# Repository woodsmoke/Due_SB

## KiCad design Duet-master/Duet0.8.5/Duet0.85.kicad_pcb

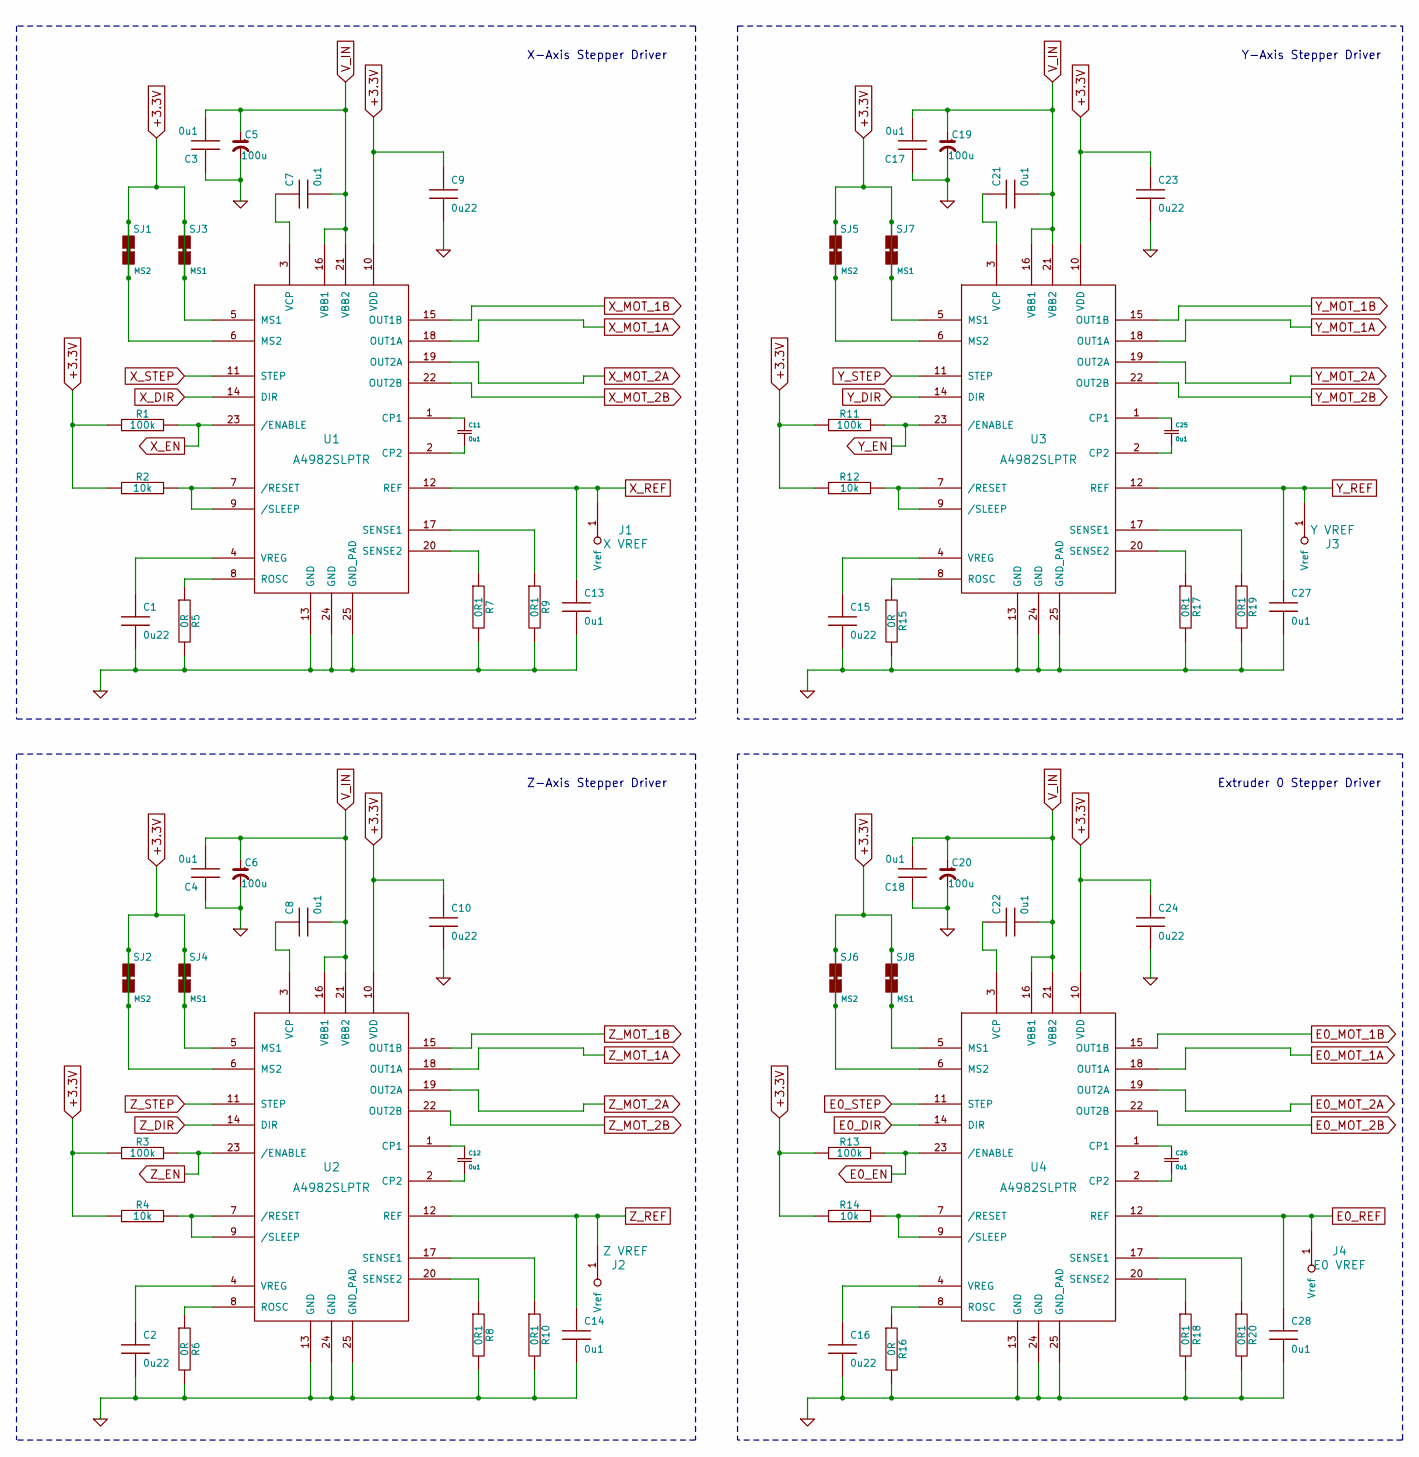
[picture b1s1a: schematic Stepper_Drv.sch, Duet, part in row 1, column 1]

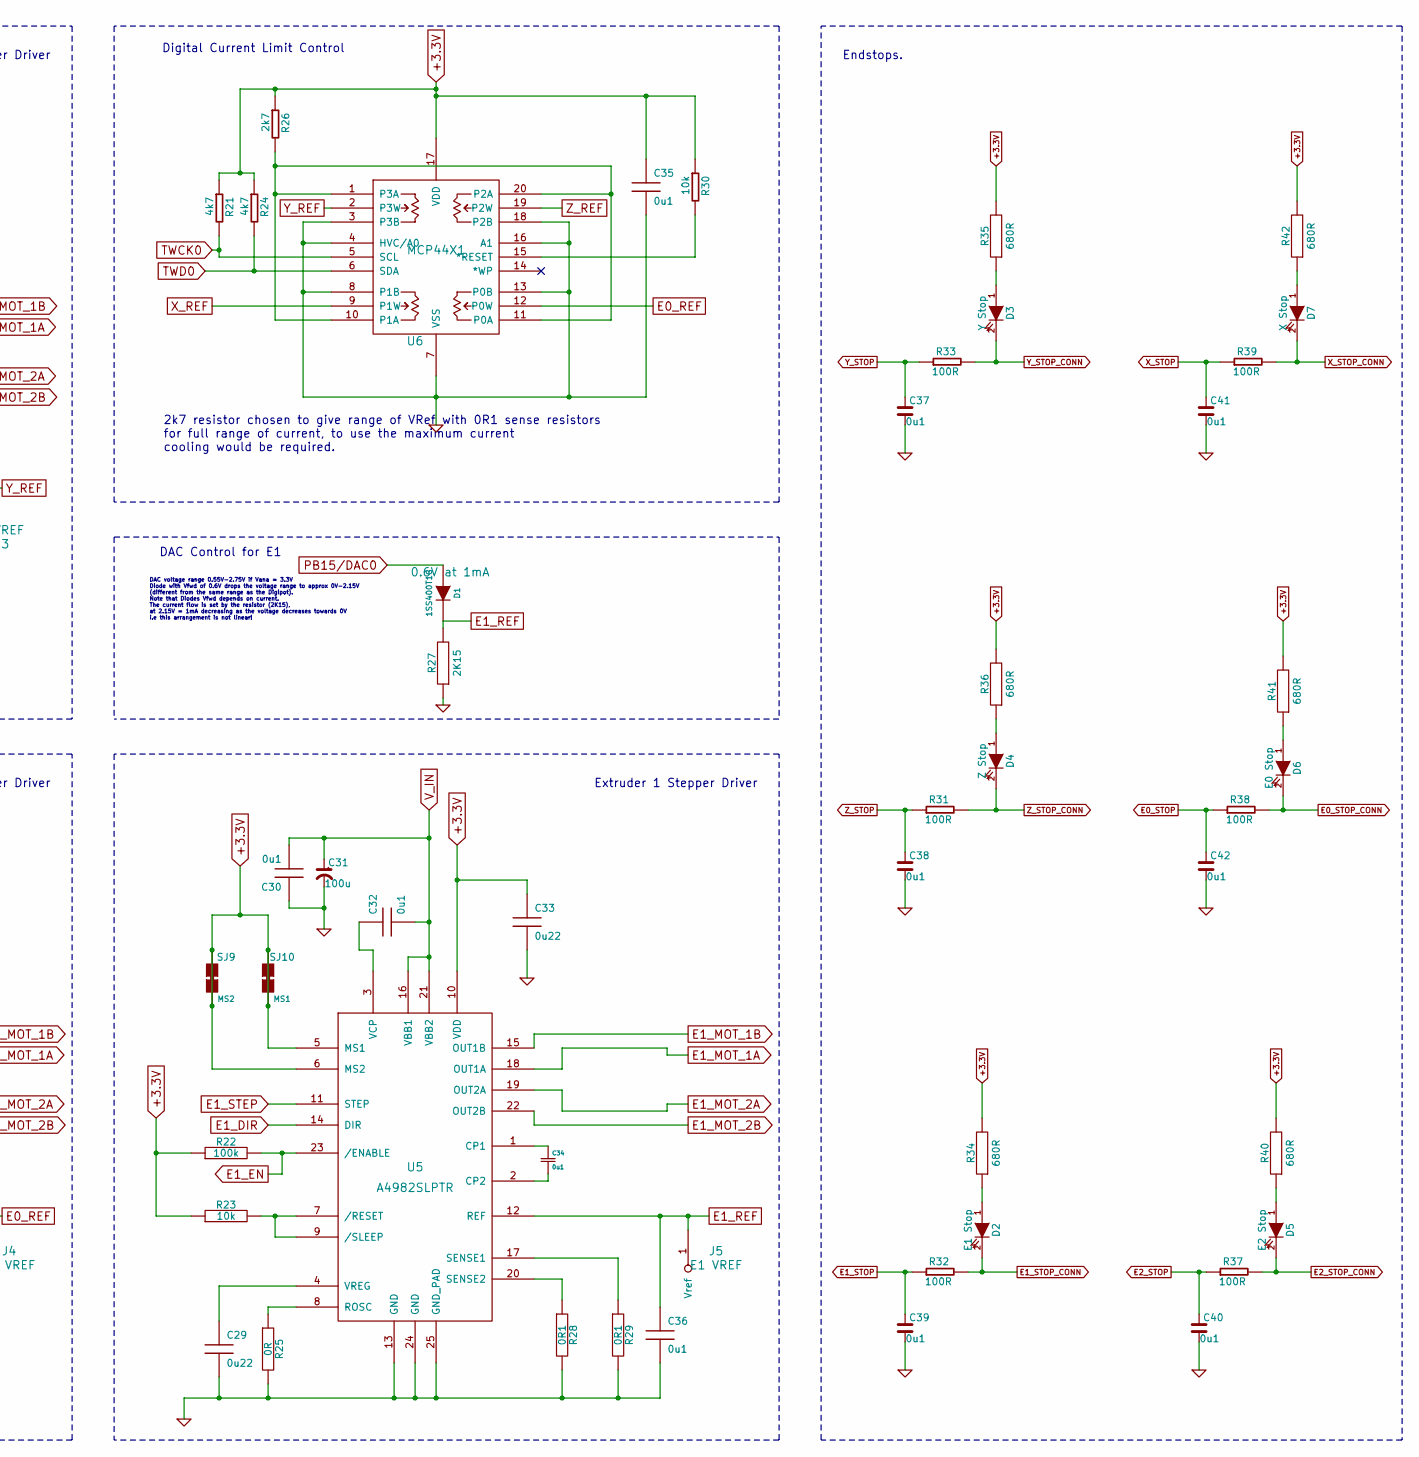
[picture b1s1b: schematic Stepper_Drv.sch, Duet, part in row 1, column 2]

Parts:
C1, C2, C9, C10, C15, C16, C23, C24, C29, C33: 0u22; 0mf22_capacitor
C3, C4, C7, C8, C11, C12, C13, C14, C17, C18, C21, C22, C25, C26, C27, C28, C30, C32, C34, C35, C36, C37, C38, C39, C40, C41, C42: 0u1; 0mf1_capacitor
C5, C6, C19, C20, C31: 100u; 100mf_capacitor
D1: 1SS400T1G; Fwd Voltage Drop (1mA) 0.6V at 1mA
D2: E1 Stop; E1STOP_diode
D3: Y Stop; YSTOP_diode
D4: Z Stop; ZSTOP_diode
D5: E2 Stop; E2STOP_diode
D6: E0 Stop; E0STOP_diode
D7: X Stop; XSTOP_diode
J1: X VREF; Vref
J2: Z VREF; Vref
J3: Y VREF; Vref
J4: E0 VREF; Vref
J5: E1 VREF; Vref
R1, R3, R11, R13, R22: 100k; 100k_R_0603
R2, R4, R12, R14, R23, R30: 10k; 10k_R_0603
R5, R6, R15, R16, R25: 0R; 0R_R_0603
R7, R8, R9, R10, R17, R18, R19, R20, R28, R29: 0R1; 0R1_R_1206
R21, R24: 4k7; 4k7_R_0603
R26: 2k7; 2k7_R_0603
R27: 2K15; 2k15_R_0603
R31: 100R; 100k_R_0603
R32, R33, R37, R38, R39: 100R; 100R_R_0603
R34, R35, R36, R40, R41, R42: 680R; 680R_R_0603
SJ1, SJ2, SJ5, SJ6, SJ9: MS2; SJump
SJ3, SJ4, SJ7, SJ8, SJ10: MS1; SJump
U1, U2, U3, U4, U5: A4982SLPTR; A4982SPLTR_TSSOP-24-thin_pads
U6: MCP44X1; MCP44X1_TSSOP-20

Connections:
+3.3V: C9.1, C10.1, C23.1, C24.1, C33.1, C35.1, R1.1, R2.1, R3.1, R4.1, R11.1, R12.1, R13.1, R14.1, R21.1, R22.1, R23.1, R24.1, R26.1, R30.1, R34.2, R35.2, R36.2, R40.2, R41.2, R42.2, SJ1.1 (SJ_P1), SJ1.2 (SJ_P2), SJ2.1 (SJ_P1), SJ2.2 (SJ_P2), SJ3.1 (SJ_P1), SJ3.2 (SJ_P2), SJ4.1 (SJ_P1), SJ4.2 (SJ_P2), SJ5.1 (SJ_P1), SJ5.2 (SJ_P2), SJ6.1 (SJ_P1), SJ6.2 (SJ_P2), SJ7.1 (SJ_P1), SJ7.2 (SJ_P2), SJ8.1 (SJ_P1), SJ8.2 (SJ_P2), SJ9.1 (SJ_P1), SJ9.2 (SJ_P2), SJ10.1 (SJ_P1), SJ10.2 (SJ_P2), U1.5 (MS1), U1.6 (MS2), U1.10 (VDD), U2.5 (MS1), U2.6 (MS2), U2.10 (VDD), U3.5 (MS1), U3.6 (MS2), U3.10 (VDD), U4.5 (MS1), U4.6 (MS2), U4.10 (VDD), U5.5 (MS1), U5.6 (MS2), U5.10 (VDD), U6.17 (VDD); also elsewhere on the board
E0_DIR: U4.14 (DIR); also elsewhere on the board
E0_EN: R13.2, U4.23 (/ENABLE); also elsewhere on the board
E0_MOT_1A: U4.18 (OUT1A); also elsewhere on the board
E0_MOT_1B: U4.15 (OUT1B); also elsewhere on the board
E0_MOT_2A: U4.19 (OUT2A); also elsewhere on the board
E0_MOT_2B: U4.22 (OUT2B); also elsewhere on the board
E0_REF: C28.1, J4.1, U4.12 (REF), U6.12 (P0W)
E0_STEP: U4.11 (STEP); also elsewhere on the board
E0_STOP: C42.1, R38.1; also elsewhere on the board
E0_STOP_CONN: D6.2 (K), R38.2; also elsewhere on the board
E1_DIR: U5.14 (DIR); also elsewhere on the board
E1_EN: R22.2, U5.23 (/ENABLE); also elsewhere on the board
E1_MOT_1A: U5.18 (OUT1A); also elsewhere on the board
E1_MOT_1B: U5.15 (OUT1B); also elsewhere on the board
E1_MOT_2A: U5.19 (OUT2A); also elsewhere on the board
E1_MOT_2B: U5.22 (OUT2B); also elsewhere on the board
E1_REF: C36.1, D1.1 (K), J5.1, R27.2, U5.12 (REF)
E1_STEP: U5.11 (STEP); also elsewhere on the board
E1_STOP: C39.1, R32.1; also elsewhere on the board
E1_STOP_CONN: D2.2 (K), R32.2; also elsewhere on the board
E2_STOP: C40.1, R37.1; also elsewhere on the board
E2_STOP_CONN: D5.2 (K), R37.2; also elsewhere on the board
GND: C1.2, C2.2, C3.1, C4.1, C5.2, C6.2, C9.2, C10.2, C13.2, C14.2, C15.2, C16.2, C17.1, C18.1, C19.2, C20.2, C23.2, C24.2, C27.2, C28.2, C29.2, C30.1, C31.2, C33.2, C35.2, C36.2, C37.2, C38.2, C39.2, C40.2, C41.2, C42.2, R5.2, R6.2, R7.2, R8.2, R9.2, R10.2, R15.2, R16.2, R17.2, R18.2, R19.2, R20.2, R25.2, R27.1, R28.2, R29.2, U1.13 (GND), U1.24 (GND), U1.25 (GND_PAD), U2.13 (GND), U2.24 (GND), U2.25 (GND_PAD), U3.13 (GND), U3.24 (GND), U3.25 (GND_PAD), U4.13 (GND), U4.24 (GND), U4.25 (GND_PAD), U5.13 (GND), U5.24 (GND), U5.25 (GND_PAD), U6.3 (P3B), U6.4 (HVC/A0), U6.7 (VSS), U6.8 (P1B), U6.13 (P0B), U6.16 (A1), U6.18 (P2B); also elsewhere on the board
unnamed: C1.1, U1.4 (VREG)
unnamed: C2.1, U2.4 (VREG)
unnamed: C7.1, U1.3 (VCP)
unnamed: C8.1, U2.3 (VCP)
unnamed: C11.1, U1.1 (CP1)
unnamed: C11.2, U1.2 (CP2)
unnamed: C12.1, U2.1 (CP1)
unnamed: C12.2, U2.2 (CP2)
unnamed: C15.1, U3.4 (VREG)
unnamed: C16.1, U4.4 (VREG)
unnamed: C21.1, U3.3 (VCP)
unnamed: C22.1, U4.3 (VCP)
unnamed: C25.1, U3.1 (CP1)
unnamed: C25.2, U3.2 (CP2)
unnamed: C26.1, U4.1 (CP1)
unnamed: C26.2, U4.2 (CP2)
unnamed: C29.1, U5.4 (VREG)
unnamed: C32.1, U5.3 (VCP)
unnamed: C34.1, U5.1 (CP1)
unnamed: C34.2, U5.2 (CP2)
unnamed: D2.1 (A), R34.1
unnamed: D3.1 (A), R35.1
unnamed: D4.1 (A), R36.1
unnamed: D5.1 (A), R40.1
unnamed: D6.1 (A), R41.1
unnamed: D7.1 (A), R42.1
unnamed: R2.2, U1.7 (/RESET), U1.9 (/SLEEP)
unnamed: R4.2, U2.7 (/RESET), U2.9 (/SLEEP)
unnamed: R5.1, U1.8 (ROSC)
unnamed: R6.1, U2.8 (ROSC)
unnamed: R7.1, U1.20 (SENSE2)
unnamed: R8.1, U2.20 (SENSE2)
unnamed: R9.1, U1.17 (SENSE1)
unnamed: R10.1, U2.17 (SENSE1)
unnamed: R12.2, U3.7 (/RESET), U3.9 (/SLEEP)
unnamed: R14.2, U4.7 (/RESET), U4.9 (/SLEEP)
unnamed: R15.1, U3.8 (ROSC)
unnamed: R16.1, U4.8 (ROSC)
unnamed: R17.1, U3.20 (SENSE2)
unnamed: R18.1, U4.20 (SENSE2)
unnamed: R19.1, U3.17 (SENSE1)
unnamed: R20.1, U4.17 (SENSE1)
unnamed: R23.2, U5.7 (/RESET), U5.9 (/SLEEP)
unnamed: R25.1, U5.8 (ROSC)
unnamed: R26.2, U6.1 (P3A), U6.10 (P1A), U6.11 (P0A), U6.20 (P2A)
unnamed: R28.1, U5.20 (SENSE2)
unnamed: R29.1, U5.17 (SENSE1)
unnamed: R30.2, U6.15 (*RESET)
PB15/DAC0: D1.2 (A); also elsewhere on the board
TWCK0: R21.2, U6.5 (SCL); also elsewhere on the board
TWD0: R24.2, U6.6 (SDA); also elsewhere on the board
V_IN: C3.2, C4.2, C5.1, C6.1, C7.2, C8.2, C17.2, C18.2, C19.1, C20.1, C21.2, C22.2, C30.2, C31.1, C32.2, U1.16 (VBB1), U1.21 (VBB2), U2.16 (VBB1), U2.21 (VBB2), U3.16 (VBB1), U3.21 (VBB2), U4.16 (VBB1), U4.21 (VBB2), U5.16 (VBB1), U5.21 (VBB2); also elsewhere on the board
X_DIR: U1.14 (DIR); also elsewhere on the board
X_EN: R1.2, U1.23 (/ENABLE); also elsewhere on the board
X_MOT_1A: U1.18 (OUT1A); also elsewhere on the board
X_MOT_1B: U1.15 (OUT1B); also elsewhere on the board
X_MOT_2A: U1.19 (OUT2A); also elsewhere on the board
X_MOT_2B: U1.22 (OUT2B); also elsewhere on the board
X_REF: C13.1, J1.1, U1.12 (REF), U6.9 (P1W)
X_STEP: U1.11 (STEP); also elsewhere on the board
X_STOP: C41.1, R39.1; also elsewhere on the board
X_STOP_CONN: D7.2 (K), R39.2; also elsewhere on the board
Y_DIR: U3.14 (DIR); also elsewhere on the board
Y_EN: R11.2, U3.23 (/ENABLE); also elsewhere on the board
Y_MOT_1A: U3.18 (OUT1A); also elsewhere on the board
Y_MOT_1B: U3.15 (OUT1B); also elsewhere on the board
Y_MOT_2A: U3.19 (OUT2A); also elsewhere on the board
Y_MOT_2B: U3.22 (OUT2B); also elsewhere on the board
Y_REF: C27.1, J3.1, U3.12 (REF), U6.2 (P3W)
Y_STEP: U3.11 (STEP); also elsewhere on the board
Y_STOP: C37.1, R33.1; also elsewhere on the board
Y_STOP_CONN: D3.2 (K), R33.2; also elsewhere on the board
Z_DIR: U2.14 (DIR); also elsewhere on the board
Z_EN: R3.2, U2.23 (/ENABLE); also elsewhere on the board
Z_MOT_1A: U2.18 (OUT1A); also elsewhere on the board
Z_MOT_1B: U2.15 (OUT1B); also elsewhere on the board
Z_MOT_2A: U2.19 (OUT2A); also elsewhere on the board
Z_MOT_2B: U2.22 (OUT2B); also elsewhere on the board
Z_REF: C14.1, J2.1, U2.12 (REF), U6.19 (P2W)
Z_STEP: U2.11 (STEP); also elsewhere on the board
Z_STOP: C38.1, R31.1; also elsewhere on the board
Z_STOP_CONN: D4.2 (K), R31.2; also elsewhere on the board

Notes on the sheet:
2k7 resistor chosen to give range of VRef with 0R1 sense resistors for full range of current, to use the maximum current cooling would be required.
Endstops.
Digital Current Limit Control
Z-Axis Stepper Driver
Extruder 0 Stepper Driver
Y-Axis Stepper Driver
X-Axis Stepper Driver
Extruder 1 Stepper Driver
DAC Control for E1
DAC voltage range 0.55V-2.75V if Vana = 3.3V Diode with Vfwd of 0.6V drops the voltage range to approx 0V-2.15V (different from the same range as the Digipot). Note that Diodes Vfwd depends on current. The current flow is set by the resistor (2K15), at 2.15V = 1mA decreasing as the voltage decrease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

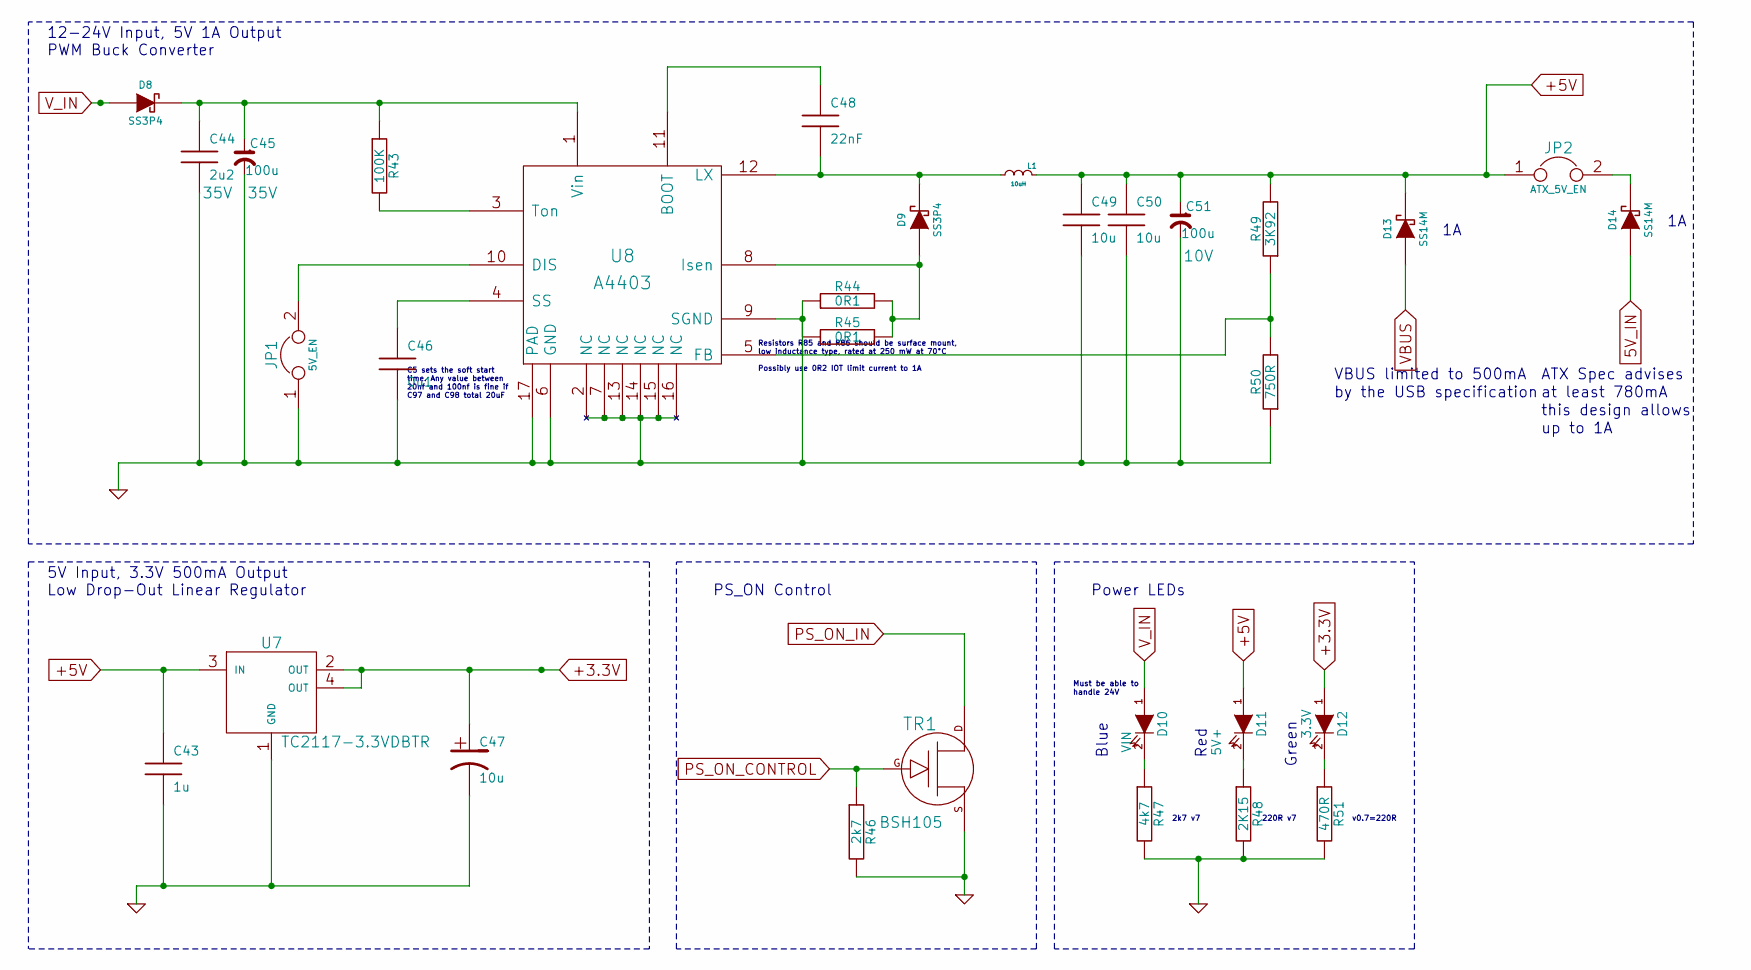
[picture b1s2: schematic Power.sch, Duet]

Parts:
C43: 1u; 1mf_capacitor
C44: 2u2; 2mf2_capacitor; Voltage 35V
C45: 100u; 100mf_capacitor; Voltage 35V
C46: 0u1; 0mf1_capacitor
C47, C49, C50: 10u; 10mf_capacitor
C48: 22nF; 22nf_capacitor
C51: 100u; 100mf_capacitor; Voltage 10V
D8, D9: SS3P4
D10: VIN; V_IN_Diode_0603
D11: 5V+; 5V_Diode_0603
D12: 3.3V; 33V_Diode_0603
D13, D14: SS14M
JP1: 5V_EN; JUMPER
JP2: ATX_5V_EN; JUMPER
L1: 10uH; 10mH_L_6x6
R43: 100K; 100k_R_0603
R44, R45: 0R1; 0R1_R_1206
R46: 2k7; 2k7_R_0603
R47: 4k7; 4k7_R_0603
R48: 2K15; 2k15_R_0603
R49: 3K92; 3k92_R_0603
R50: 750R; 750R_R_0603
R51: 470R; 470R_R_0603
TR1: BSH105; BSH105_SOT-23
U7: TC2117-3.3VDBTR
U8: A4403; A4403_QFN16-4x4

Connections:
5V_IN: D14.1 (A); also elsewhere on the board
+3.3V: C47.1, D12.1 (A), U7.2 (OUT), U7.4 (OUT); also elsewhere on the board
+5V: C43.1, C49.1, C50.1, C51.1, D11.1 (A), D13.2 (K), JP2.1, L1.1 (A), R49.2, U7.3 (IN); also elsewhere on the board
GND: C43.2, C44.2, C45.2, C46.2, C47.2, C49.2, C50.2, C51.2, JP1.1, R44.1, R45.1, R46.2, R47.2, R48.2, R50.1, R51.2, TR1.S, U7.1 (GND), U8.2 (NC), U8.6 (GND), U8.7 (NC), U8.9 (SGND), U8.13 (NC), U8.14 (NC), U8.15 (NC), U8.16 (NC), U8.17 (PAD); also elsewhere on the board
unnamed: C44.1, C45.1, D8.2 (K), R43.1, U8.1 (Vin)
unnamed: C46.1, U8.4 (SS)
unnamed: C48.1, U8.11 (BOOT)
unnamed: C48.2, D9.2 (K), L1.2 (B), U8.12 (LX)
unnamed: D9.1 (A), R44.2, R45.2, U8.8 (Isen)
unnamed: D10.2 (K), R47.1
unnamed: D11.2 (K), R48.1
unnamed: D12.2 (K), R51.1
unnamed: D14.2 (K), JP2.2
unnamed: JP1.2, U8.10 (DIS)
unnamed: R43.2, U8.3 (Ton)
unnamed: R49.1, R50.2, U8.5 (FB)
PS_ON_CONTROL: R46.1, TR1.G; also elsewhere on the board
PS_ON_IN: TR1.D; also elsewhere on the board
VBUS: D13.1 (A); also elsewhere on the board
V_IN: D8.1 (A), D10.1 (A); also elsewhere on the board

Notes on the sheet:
PS_ON Control
up to 1A
this design allows
at least 780mA
ATX Spec advises
by the USB specification
VBUS limited to 500mA
5V Input, 3.3V 500mA Output Low Drop-Out Linear Regulator
12-24V Input, 5V 1A Output PWM Buck Converter
2k7 v7
220R v7
v0.7=220R
Resistors R85 and R86 should be surface mount, low inductance type, rated at 250 mW at 70°C Possibly use 0R2 IOT limit current to 1A
C5 sets the soft start time. Any value between 20nf and 100nf is fine if C97 and C98 total 20uF
Power LEDs
Must be able to handle 24V
Blue
Red
Green

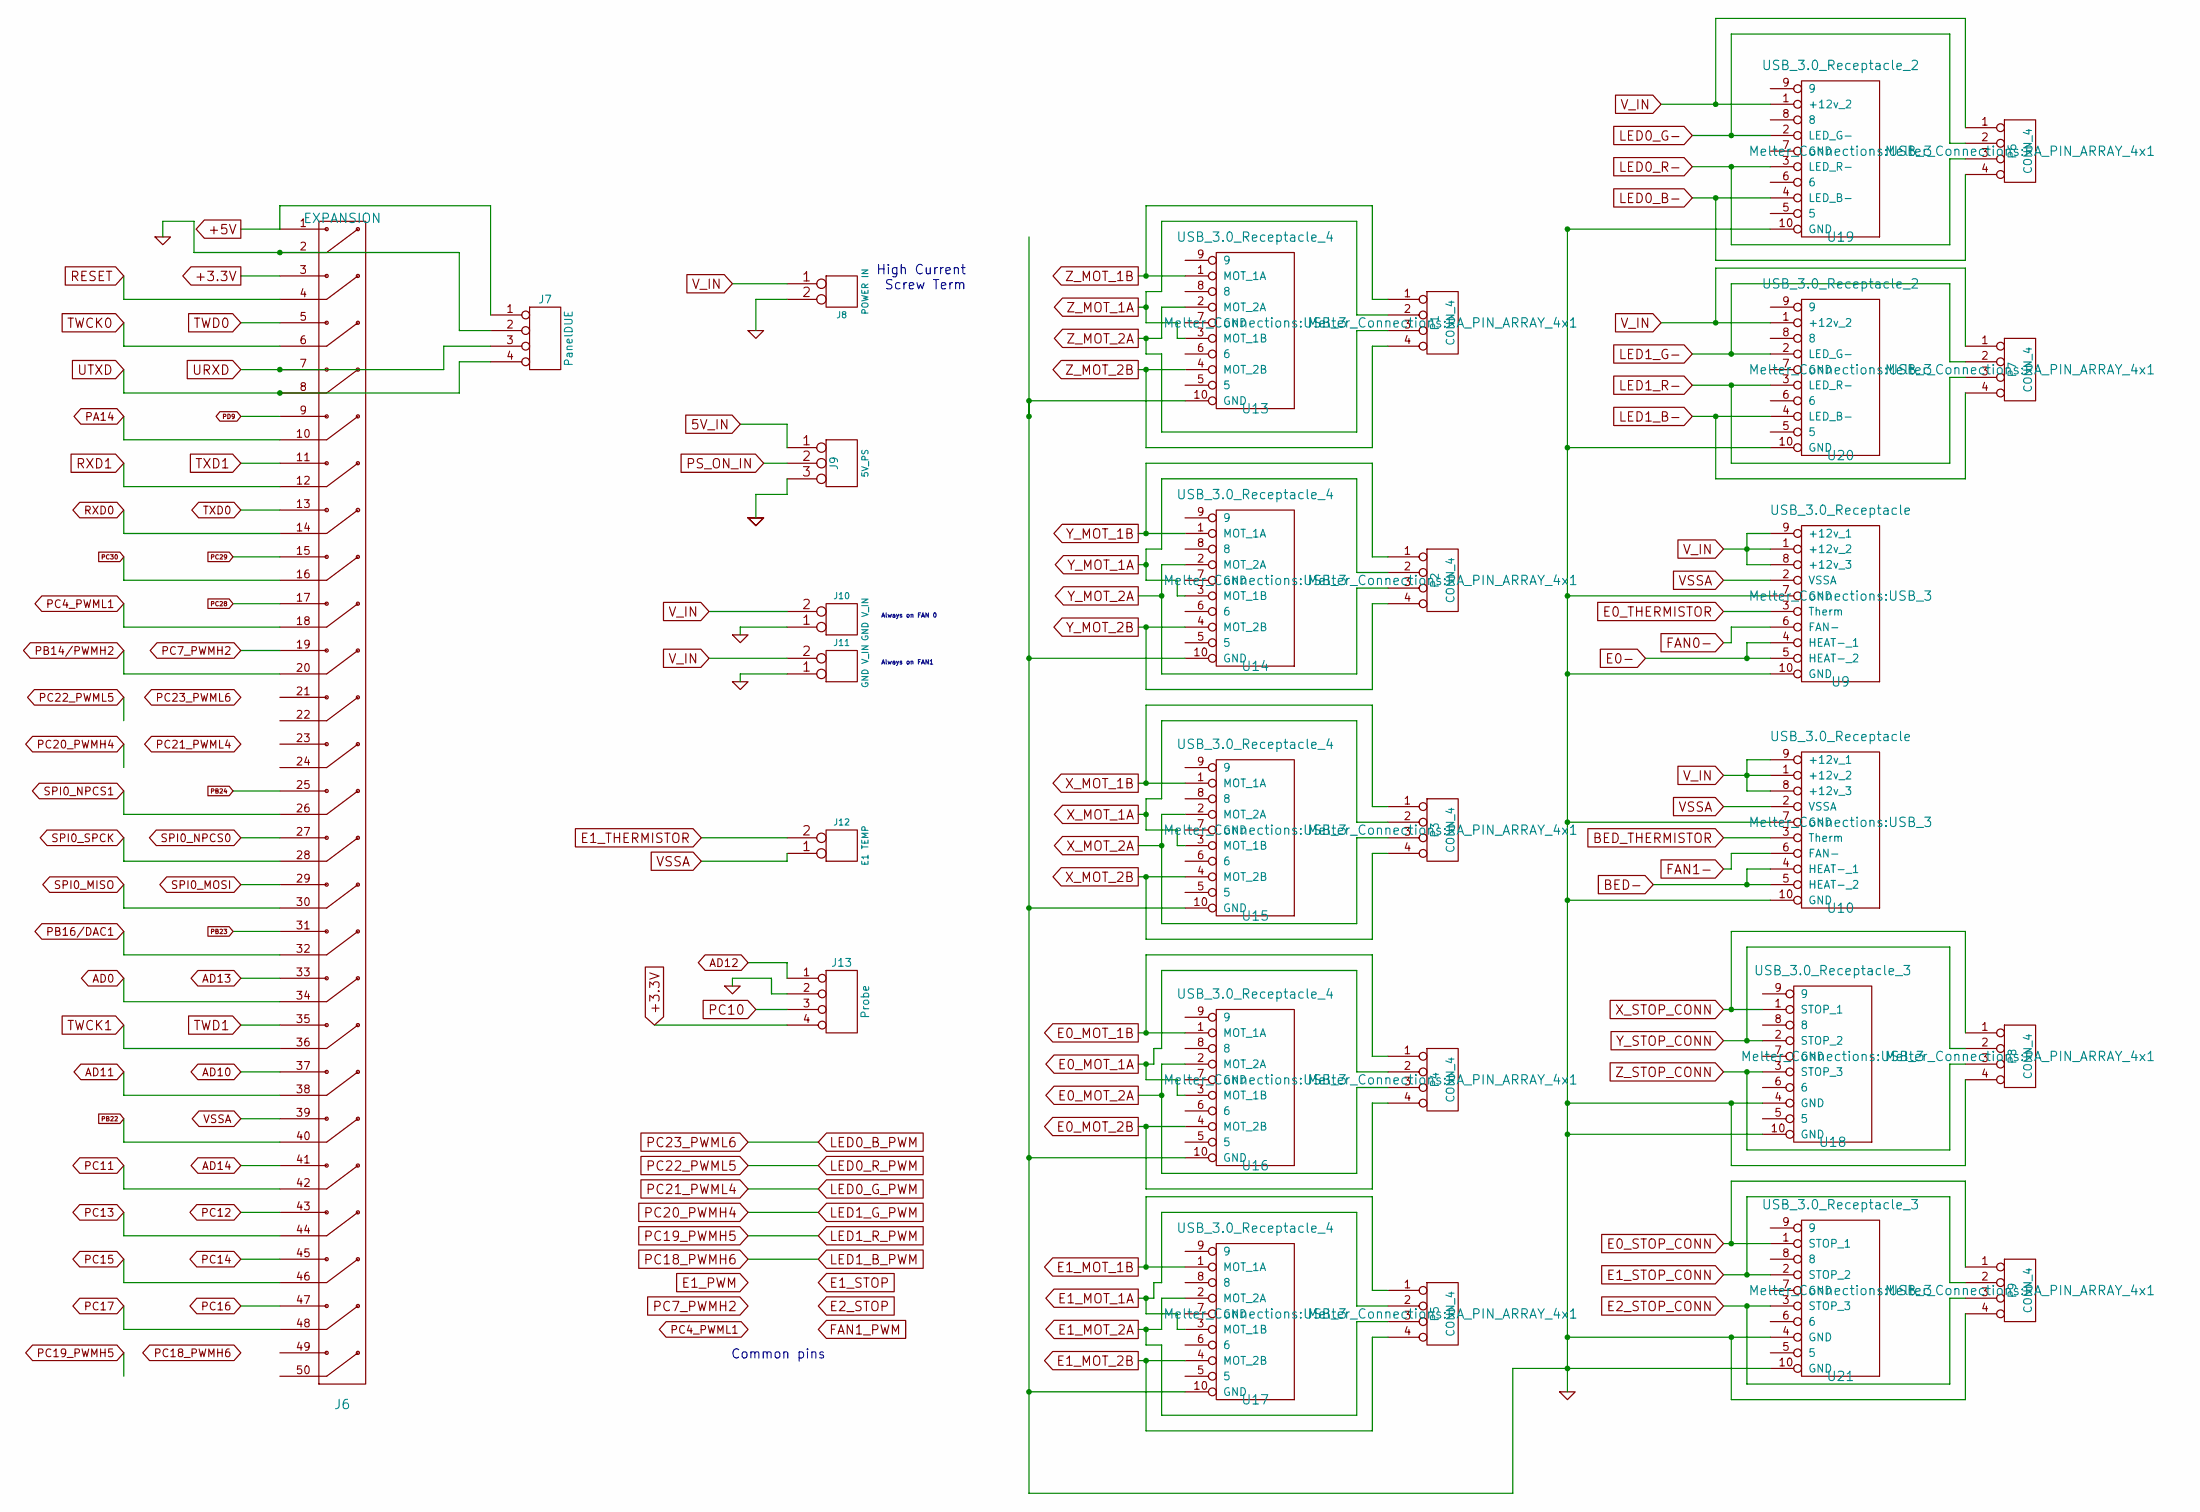
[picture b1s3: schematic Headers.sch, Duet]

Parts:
J6: EXPANSION; PIN_ARRAY_25X2
J7: PanelDUE; PIN_ARRAY_4x1
J8: POWER IN; V_TERM_2-WAY_6.35mm
J9: 5V_PS; 5VPSGND_PIN_ARRAY_3X1
J10, J11: GND V_IN; JUMPER
J12: E1 TEMP; PIN_ARRAY_2X1
J13: Probe; PIN_ARRAY_4x1
P1, P2, P3, P4, P5, P6, P7, P8, P9: CONN_4; RA_PIN_ARRAY_4x1
U9, U10: USB_3.0_Receptacle; USB_3
U13, U14, U15, U16, U17: USB_3.0_Receptacle_4; USB_3
U18, U21: USB_3.0_Receptacle_3; USB_3
U19, U20: USB_3.0_Receptacle_2; USB_3

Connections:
5V_IN: J9.1; also elsewhere on the board
+3.3V: J6.3, J13.4; also elsewhere on the board
+5V: J6.1, J7.1; also elsewhere on the board
AD0: J6.34; also elsewhere on the board
AD10: J6.37; also elsewhere on the board
AD11: J6.38; also elsewhere on the board
AD12: J13.1; also elsewhere on the board
AD13: J6.33; also elsewhere on the board
AD14: J6.41; also elsewhere on the board
E1_THERMISTOR: J12.2 (PM); also elsewhere on the board
GND: J6.2, J7.2, J8.2 (PM), J9.3, J10.1, J11.1, J13.2, P8.4, P9.4, U9.7 (GND), U9.10 (GND), U10.7 (GND), U10.10 (GND), U13.10 (GND), U14.10 (GND), U15.10 (GND), U16.10 (GND), U17.10 (GND), U18.4 (GND), U18.10 (GND), U19.10 (GND), U20.10 (GND), U21.4 (GND), U21.10 (GND); also elsewhere on the board
unnamed: P1.1, U13.1 (MOT_1A)
unnamed: P1.2, U13.3 (MOT_1B)
unnamed: P1.3, U13.2 (MOT_2A)
unnamed: P1.4, U13.4 (MOT_2B)
unnamed: P2.1, U14.1 (MOT_1A)
unnamed: P2.2, U14.3 (MOT_1B)
unnamed: P2.3, U14.2 (MOT_2A)
unnamed: P2.4, U14.4 (MOT_2B)
unnamed: P3.1, U15.1 (MOT_1A)
unnamed: P3.2, U15.3 (MOT_1B)
unnamed: P3.3, U15.2 (MOT_2A)
unnamed: P3.4, U15.4 (MOT_2B)
unnamed: P4.1, U16.1 (MOT_1A)
unnamed: P4.2, U16.3 (MOT_1B)
unnamed: P4.3, U16.2 (MOT_2A)
unnamed: P4.4, U16.4 (MOT_2B)
unnamed: P5.1, U17.1 (MOT_1A)
unnamed: P5.2, U17.3 (MOT_1B)
unnamed: P5.3, U17.2 (MOT_2A)
unnamed: P5.4, U17.4 (MOT_2B)
unnamed: P6.2, U19.2 (LED_G-)
unnamed: P6.3, U19.3 (LED_R-)
unnamed: P6.4, U19.4 (LED_B-)
unnamed: P7.2, U20.2 (LED_G-)
unnamed: P7.3, U20.3 (LED_R-)
unnamed: P7.4, U20.4 (LED_B-)
unnamed: P8.1, U18.1 (STOP_1)
unnamed: P8.2, U18.2 (STOP_2)
unnamed: P8.3, U18.3 (STOP_3)
unnamed: P9.1, U21.1 (STOP_1)
unnamed: P9.2, U21.2 (STOP_2)
unnamed: P9.3, U21.3 (STOP_3)
unnamed: U9.4 (HEAT-_1), U9.5 (HEAT-_2)
unnamed: U10.4 (HEAT-_1), U10.5 (HEAT-_2)
PA14: J6.10; also elsewhere on the board
PB14/PWMH2: J6.20; also elsewhere on the board
PB16/DAC1: J6.32; also elsewhere on the board
PB22: J6.40; also elsewhere on the board
PB23: J6.31; also elsewhere on the board
PB24: J6.25; also elsewhere on the board
PC4_PWML1: J6.18
PC7_PWMH2: J6.19
PC10: J13.3; also elsewhere on the board
PC11: J6.42; also elsewhere on the board
PC12: J6.43; also elsewhere on the board
PC13: J6.44; also elsewhere on the board
PC14: J6.45; also elsewhere on the board
PC15: J6.46; also elsewhere on the board
PC16: J6.47; also elsewhere on the board
PC17: J6.48; also elsewhere on the board
PC28: J6.17; also elsewhere on the board
PC29: J6.15; also elsewhere on the board
PC30: J6.16; also elsewhere on the board
PD9: J6.9; also elsewhere on the board
PS_ON_IN: J9.2 (PM); also elsewhere on the board
RESET: J6.4; also elsewhere on the board
RXD0: J6.14; also elsewhere on the board
RXD1: J6.12; also elsewhere on the board
SPI0_MISO: J6.30; also elsewhere on the board
SPI0_MOSI: J6.29; also elsewhere on the board
SPI0_NPCS0: J6.27; also elsewhere on the board
SPI0_NPCS1: J6.26; also elsewhere on the board
SPI0_SPCK: J6.28; also elsewhere on the board
TWCK0: J6.6; also elsewhere on the board
TWCK1: J6.36; also elsewhere on the board
TWD0: J6.5; also elsewhere on the board
TWD1: J6.35; also elsewhere on the board
TXD0: J6.13; also elsewhere on the board
TXD1: J6.11; also elsewhere on the board
URXD: J6.7, J7.3; also elsewhere on the board
UTXD: J6.8, J7.4; also elsewhere on the board
VSSA: J6.39, J12.1, U9.2 (VSSA), U10.2 (VSSA); also elsewhere on the board
V_IN: J8.1, J10.2 (PM), J11.2 (PM), P6.1, P7.1, U9.1 (+12v_2), U9.8 (+12v_3), U9.9 (+12v_1), U10.1 (+12v_2), U10.8 (+12v_3), U10.9 (+12v_1), U19.1 (+12v_2), U20.1 (+12v_2); also elsewhere on the board

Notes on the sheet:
High Current Screw Term
Always on FAN 0
Common pins
Always on FAN1

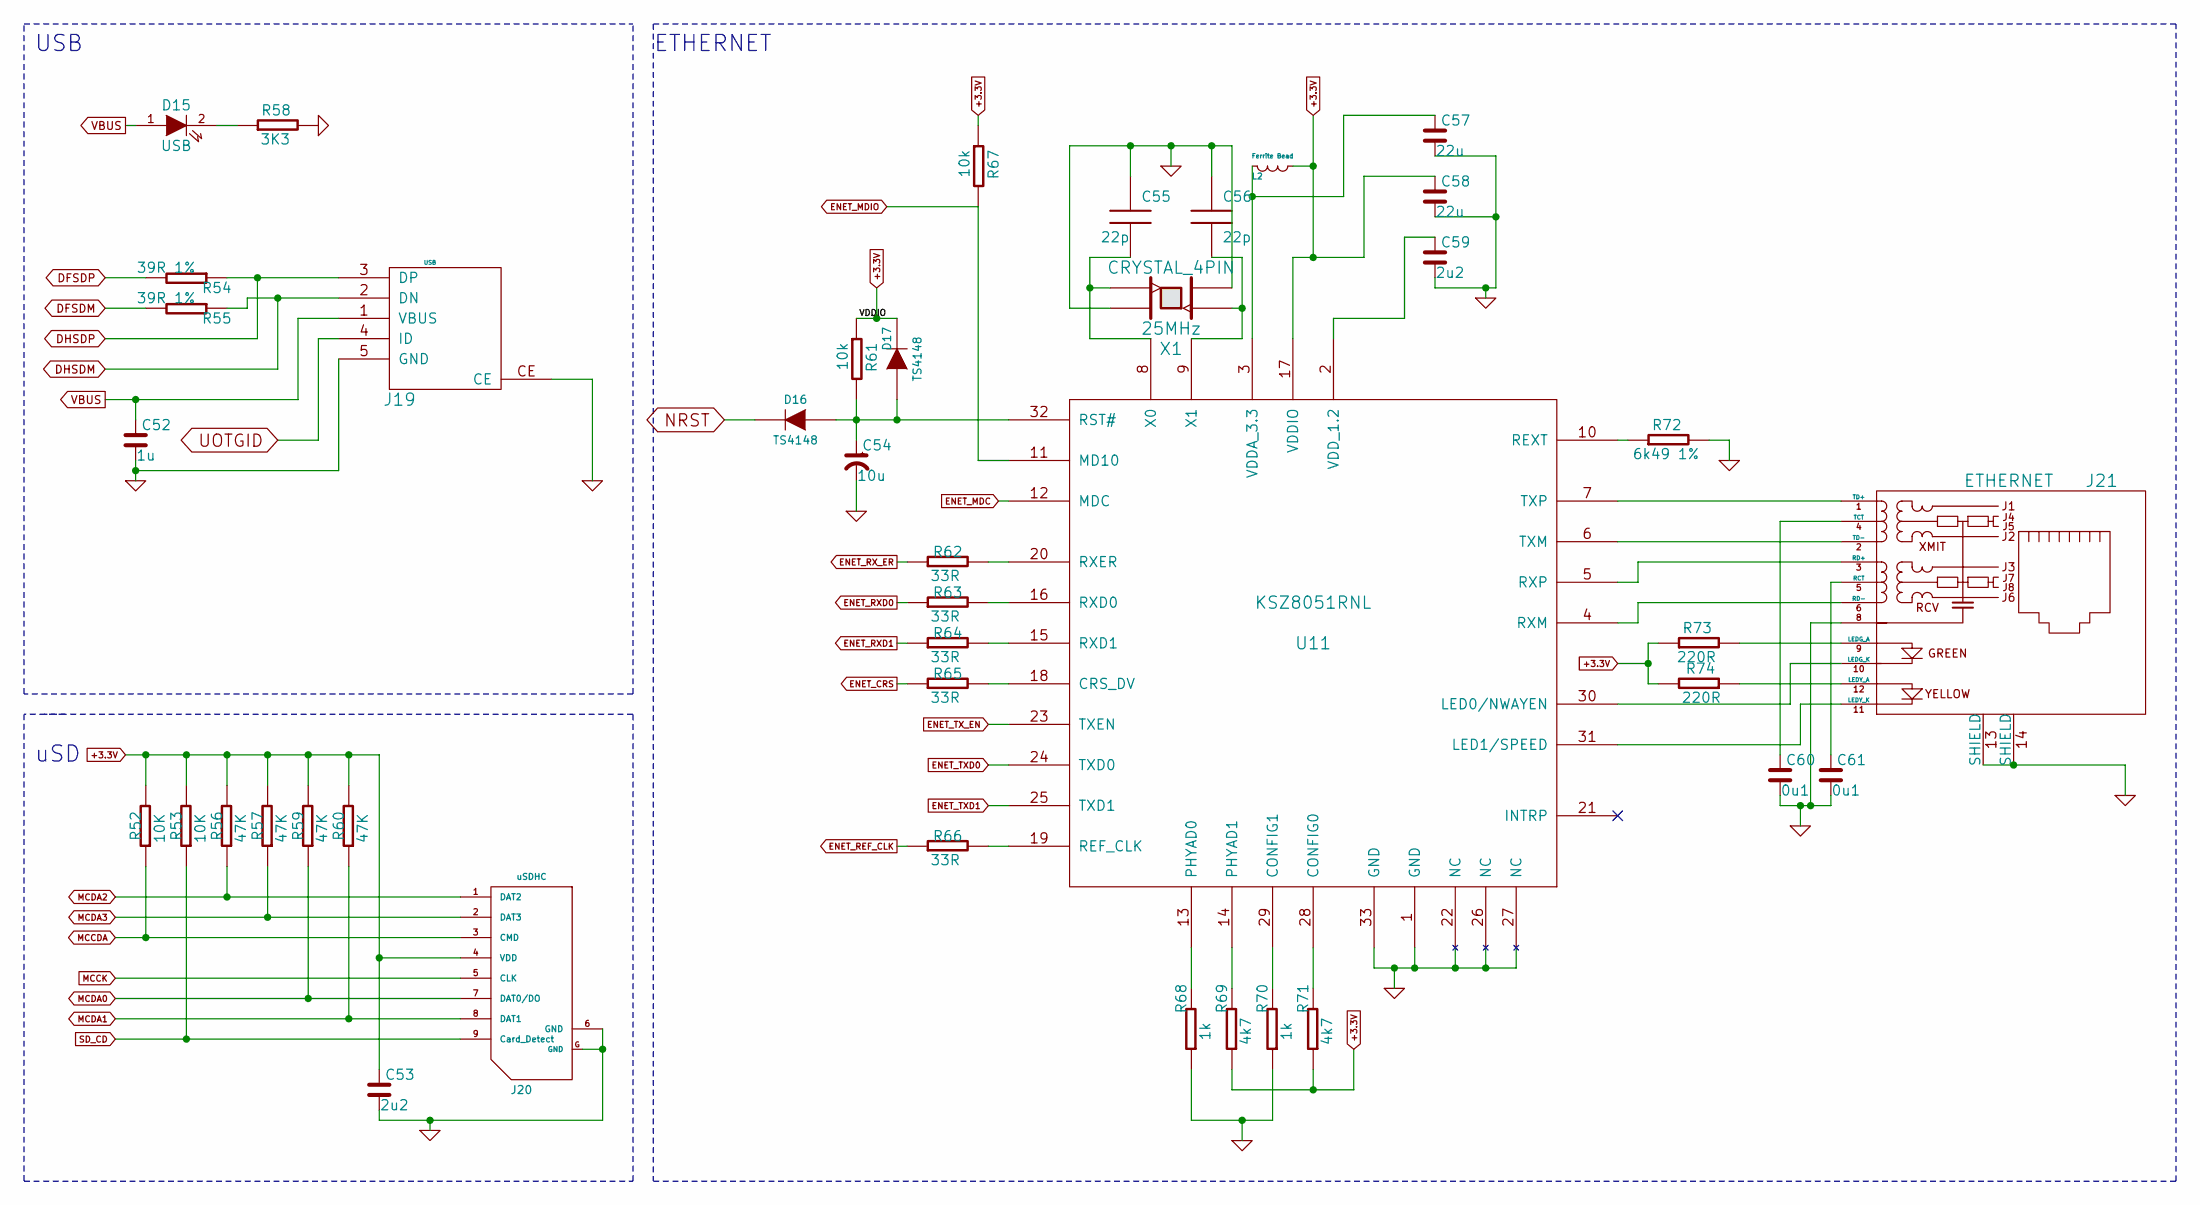
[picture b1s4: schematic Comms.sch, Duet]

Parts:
C52: 1u; 1mf_capacitor
C53, C59: 2u2; 2mf2_capacitor
C54: 10u; 10mf_capacitor
C55, C56: 22p; 22pf_capacitor
C57, C58: 22u; 22mf_Capacitor_1210
C60, C61: 0u1; 0mf1_capacitor
D15: USB; USB_Diode_0603
D16, D17: TS4148; TS4148_Diode_0805
J19: USB; uSD_SKT
J20: uSDHC; SD_Card_Receptacle
J21: ETHERNET; RJ45_MAG
L2: Ferrite Bead; FERRITE_BEAD
R52, R53: 10K; 10k_R_0603
R54, R55: 39R 1%; 39_1per_R_0603
R56, R57, R59, R60: 47K; 47k_R_0603
R58: 3K3; 3k3_R_0603
R61, R67: 10k; 10k_R_0603
R62, R63, R64, R65, R66: 33R; 33R_R_0603
R68, R70: 1k; 1k_R_0603
R69, R71: 4k7; 4k7_R_0603
R72: 6k49 1%; 6k49_1_per_R_0603
R73, R74: 220R; 220R_R_0603
U11: KSZ8051RNL
X1: CRYSTAL_4PIN; Xtal_5x3.2

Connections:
+3.3V: C53.1, C58.1, D17.1 (K), J20.4 (VDD), L2.2 (B), R52.2, R53.2, R56.2, R57.2, R59.2, R60.2, R61.1, R67.1, R69.1, R71.1, R73.1, R74.2, U11.17 (VDDIO); also elsewhere on the board
DFSDM: R55.2; also elsewhere on the board
DFSDP: R54.2; also elsewhere on the board
DHSDM: J19.2 (DN), R55.1; also elsewhere on the board
DHSDP: J19.3 (DP), R54.1; also elsewhere on the board
ENET_CRS: R65.1; also elsewhere on the board
ENET_MDC: U11.12 (MDC); also elsewhere on the board
ENET_MDIO: R67.2, U11.11 (MD10); also elsewhere on the board
ENET_REF_CLK: R66.1; also elsewhere on the board
ENET_RXD0: R63.1; also elsewhere on the board
ENET_RXD1: R64.1; also elsewhere on the board
ENET_RX_ER: R62.1; also elsewhere on the board
ENET_TXD0: U11.24 (TXD0); also elsewhere on the board
ENET_TXD1: U11.25 (TXD1); also elsewhere on the board
ENET_TX_EN: U11.23 (TXEN); also elsewhere on the board
GND: C52.2, C53.2, C54.2, C55.1, C56.1, C57.2, C58.2, C59.2, C60.2, C61.2, J19.5 (GND), J19.CE, J20.6 (GND), J20.G (GND), J21.8, J21.13 (SHIELD), J21.14 (SHIELD), R58.2, R68.1, R70.1, R72.2, U11.1 (GND), U11.22 (NC), U11.26 (NC), U11.27 (NC), U11.33 (GND), X1.2, X1.4; also elsewhere on the board
MCCDA: J20.3 (CMD), R52.1; also elsewhere on the board
MCCK: J20.5 (CLK); also elsewhere on the board
MCDA0: J20.7 (DAT0/DO), R59.1; also elsewhere on the board
MCDA1: J20.8 (DAT1), R60.1; also elsewhere on the board
MCDA2: J20.1 (DAT2), R56.1; also elsewhere on the board
MCDA3: J20.2 (DAT3), R57.1; also elsewhere on the board
NRST: D16.1 (K); also elsewhere on the board
unnamed: C54.1, D16.2 (A), D17.2 (A), R61.2, U11.32 (RST#)
unnamed: C55.2, U11.8 (X0), X1.3
unnamed: C56.2, U11.9 (X1), X1.1
unnamed: C57.1, L2.1 (A), U11.3 (VDDA_3.3)
unnamed: C59.1, U11.2 (VDD_1.2)
unnamed: C60.1, J21.4 (TCT)
unnamed: C61.1, J21.5 (RCT)
unnamed: D15.2 (K), R58.1
unnamed: J21.1 (TD+), U11.7 (TXP)
unnamed: J21.2 (TD-), U11.6 (TXM)
unnamed: J21.3 (RD+), U11.5 (RXP)
unnamed: J21.6 (RD-), U11.4 (RXM)
unnamed: J21.9 (LEDG_A), R73.2
unnamed: J21.10 (LEDG_K), U11.30 (LED0/NWAYEN)
unnamed: J21.11 (LEDY_K), U11.31 (LED1/SPEED)
unnamed: J21.12 (LEDY_A), R74.1
unnamed: R62.2, U11.20 (RXER)
unnamed: R63.2, U11.16 (RXD0)
unnamed: R64.2, U11.15 (RXD1)
unnamed: R65.2, U11.18 (CRS_DV)
unnamed: R66.2, U11.19 (REF_CLK)
unnamed: R68.2, U11.13 (PHYAD0)
unnamed: R69.2, U11.14 (PHYAD1)
unnamed: R70.2, U11.29 (CONFIG1)
unnamed: R71.2, U11.28 (CONFIG0)
unnamed: R72.1, U11.10 (REXT)
SD_CD: J20.9 (Card_Detect), R53.1; also elsewhere on the board
UOTGID: J19.4 (ID); also elsewhere on the board
VBUS: C52.1, D15.1 (A), J19.1 (VBUS); also elsewhere on the board

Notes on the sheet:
uSD
ETHERNET
USB
